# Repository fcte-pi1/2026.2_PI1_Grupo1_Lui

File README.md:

# Projeto Integrador 1 - 2026.2 | Grupo 01 | Prof. Lui

<div align="center">

  # Projeto Integrador 1 — Micromouse (Grupo 1)
  **Semestre 2026.2 | Universidade de Brasília (UnB) | Prof. Lui**

</div>

---

> **Aviso ao Professor:** Este é o repositório oficial do Grupo 01 utilizado para o desenvolvimento do projeto de PI1 (Micromouse) durante o semestre 2026.2. Todo o histórico de commits, código-fonte e detalhamentos estão centralizados aqui.

## 🤖 Sobre o Projeto
O projeto consiste no desenvolvimento completo de um robô autônomo (Micromouse) capaz de navegar e resolver um labirinto, integrando conhecimentos de quatro grandes áreas da engenharia: **Software, Eletrônica, Energia e Estruturas**.

Toda a documentação gerencial e conceitual (TAP, Requisitos, EAP, Cronograma, Testes, etc.) está centralizada de forma interativa no nosso **[Site de Documentação Oficial](https://fcte-pi1.github.io/2026.2_PI1_Grupo1_Lui/)**.

## 🗂️ Estrutura do Repositório
Para manter o padrão e a facilidade de busca, o repositório está dividido nas seguintes pastas:

* 📂 **`docs/`** — Arquivos Markdown (`.md`) e ativos que alimentam a página web.
* 📂 **`hw/`** — Arquitetura de hardware, esquemáticos e arquivos de simulação de circuitos.
* 📂 **`mec/`** — Modelagens 3D, arquivos CAD e projetos de estrutura.
* 📂 **`src/`** — Código-fonte e algoritmos de navegação/controle do robô.

*(A estrutura de pastas não isola as equipes. O projeto é multidisciplinar e os membros devem trabalhar nas diferentes pastas conforme a necessidade das tarefas).*

## 👥 Equipe
O time é formado por estudantes de engenharia e dividido em subáreas para facilitar o gerenciamento técnico, atuando sob a liderança geral de **Antônio Lucas** e apoio dos subgerentes:

* 💻 **Software:** Pedro Ian (Subgerente)
* ⚡ **Energia:** Rafaela Trajano (Subgerente)
* 🔌 **Eletrônica:** Leonardo Augusto (Subgerente)
* 🏗️ **Estruturas:** Carlos Henrique (Subgerente)

<details>
<summary><b>Clique aqui para ver a lista completa com os 19 integrantes</b></summary>

* Humberto Alencar (Aeroespacial)
* João Vitor Sales Ibiapina (Software)
* Eduardo Lobo Moreira (Software)
* Pedro Ian (Software)
* Breno Teixeira (Software)
* Rafaela Trajano Ruas (Energia)
* Lucas Oliveira de Paula (Software)
* Carlos Henrique de Paiva Muniz (Software)
* Mariana Solano de Brito Elias (Aeroespacial)
* Antônio José Magalhães Leão Júnior (Software)
* João Pedro Jaime (Software)
* Lucas Peixoto Rodrigues (Software)
* Daniel Almeida Frota (Software)
* Antônio Lucas De Araújo Lima (Software)
* Pedro Franco Cavalcanti Rêgo (Software)
* Alexandre Henrique Almeida Valadares Sousa (Software)
* Davi Sakai (Software)
* Gustavo Antônio (Software)
* Leonardo Augusto (Eletrônica)

</details>

## 🚀 Para os Integrantes: Como Contribuir

A organização e a correta utilização do repositório serão consideradas na avaliação do grupo. Dessa forma, é fundamental que **todos** utilizem o Git de forma alinhada com a estratégia da equipe.

### Fluxo de Trabalho
1. **Clone o repositório:** Após obter acesso (via convite no e-mail ou notificação), abra o terminal e clone o projeto:
   ```bash
   git clone [https://github.com/fcte-pi1/2026.2_PI1_Grupo1_Lui.git](https://github.com/fcte-pi1/2026.2_PI1_Grupo1_Lui.git)

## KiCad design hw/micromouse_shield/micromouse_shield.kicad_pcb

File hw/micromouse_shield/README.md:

# Projeto KiCad — PCB Shield do Micromouse (Grupo 1)

Este diretório contém os arquivos de projeto da placa de circuito impresso (**PCB Shield customizada**) do robô autônomo Micromouse para a disciplina **PI1 (2026.2, FCTE/UnB, Prof. Lui)**.

O projeto é 100% compatível com as versões **KiCad v7, v8, v9 e v10** com biblioteca embutida (*Self-Contained*), permitindo que qualquer integrante da equipe (inclusive de Software) abra e visualize o esquemático em qualquer computador sem precisar instalar bibliotecas externas. Além disso, um arquivo PDF já renderizado está disponível no próprio diretório para visualização imediata.

---

## 1. Estrutura dos Arquivos

```
hw/micromouse_shield/
├── micromouse_shield.kicad_pro        # Arquivo de configuração e metadados do projeto KiCad
├── micromouse_shield.kicad_sch        # Esquemático elétrico oficial sincronizado (Rev 2.0)
├── micromouse_shield_VERSION2.kicad_sch # Arquivo de esquemático Rev 2.0 (com proteções e Buck)
├── micromouse_shield.kicad_pcb        # PCB populada com todos os footprints oficiais, posições e furos M3
├── micromouse_shield.pdf              # PDF em alta resolução do esquemático para consulta rápida
├── micromouse_shield_sch.png          # Imagem PNG em alta resolução (300 DPI) do esquemático Rev 2.0
├── micromouse_shield_3d.png           # Renderização 3D oficial da placa Shield montada
├── micromouse_shield.net              # Netlist elétrica para verificação e importação
├── diagrama_blocos_hardware.png       # Imagem em alta resolução do Diagrama de Blocos do robô
├── diagrama_blocos_hardware.tex       # Código-fonte TikZ (LaTeX Standalone) do Diagrama de Blocos
├── diagrama_blocos_hardware.mmd       # Código-fonte Mermaid do Diagrama de Blocos
├── generate_schematic.py              # Script Python reprodutível gerador do esquemático
├── generate_pcb.py                    # Script Python reprodutível gerador da PCB via pcbnew nativo
└── README.md                          # Guia de montagem e instruções de layout
```

---

## 2. Como Abrir e Visualizar no KiCad

1. No terminal do CachyOS/Linux (ou no menu de aplicativos), execute:
   ```bash
   kicad hw/micromouse_shield/micromouse_shield.kicad_pro
   ```
2. Na janela principal do KiCad:
   - Dê duplo clique em **`micromouse_shield.kicad_sch`** (ou abra `micromouse_shield_VERSION2.kicad_sch`) para abrir o editor esquemático (**Eeschema**);
   - Ou dê duplo clique em **`micromouse_shield.kicad_pcb`** para abrir o editor de PCB (**Pcbnew**);
3. Dica rápida: Se quiser apenas consultar as conexões sem abrir o KiCad, abra diretamente o arquivo [`micromouse_shield.pdf`](file:///home/eduardolm/Documents/2026.2_PI1_Grupo1_Lui/hw/micromouse_shield/micromouse_shield.pdf) ou visualize [`micromouse_shield_sch.png`](file:///home/eduardolm/Documents/2026.2_PI1_Grupo1_Lui/hw/micromouse_shield/micromouse_shield_sch.png).

---

## 3. Arquitetura do Esquemático e Mapeamento de Redes (*Nets*) (Rev 2.0)

O circuito adota a topologia **100% Plug & Play**, utilizando apenas barras de pinos fêmea (soquetes de 2,54 mm) para receber módulos prontos e conectores com trava:

| Bloco Funcional | Referência | Componente / Módulo | Conexões e Rótulos de Redes (*Nets*) |
|---|:---:|---|---|
| **Processamento Central** | `J_ESP_L` e `J_ESP_R` | Barras Fêmea 1x15 para ESP32 DevKit V1 | Todos os 30 pinos mapeados, com GPIO 12 isolado contra travamento de boot. |
| **Driver de Motores** | `J_DRV_CTRL` e `J_DRV_PWR` | Barras Fêmea 1x08 para módulo TB6612FNG | PWM (`PWMA`, `PWMB`), Direção (`AIN1/2`, `BIN1/2`), saídas dos motores e alimentação $V_{MOT}$. |
| **IMU Inercial** | `U_IMU` | Barra Fêmea 1x08 para GY-521 (MPU6050) | $I^2C$ (`I2C_SDA` no GPIO 21, `I2C_SCL` no GPIO 22) e alimentação de 3,3 V. |
| **Sensores de Distância** | `J_TOF_F`, `J_TOF_L`, `J_TOF_R` | Barras Macho 1x05 para 3x VL53L0X | $I^2C$ compartilhado + pinos de corte dinâmico `XSHUT_F` (GPIO 32), `XSHUT_L` (GPIO 13), `XSHUT_R` (GPIO 14). |
| **Atuadores e Encoders** | `J_MOT_L` e `J_MOT_R` | Conectores JST 1x06 para motores N20 | Alimentação de motor e sinais de quadratura alimentados estritamente em **3,3 V** (`ENC_L_A/B` e `ENC_R_A/B`). |
| **Entrada de Bateria** | `TB_PWR1` | Borne/Conector Polarizado 2 vias | 1: $V_{BAT}+$ (7,4 V), 2: $GND$. |
| **Proteção por Fusível** | `F1` | Fusível Rearmável 3A | Em série com o polo positivo da bateria. |
| **Chave Geral Mecânica** | `SW1` | Chave Mecânica Liga/Desliga | Interrupção física do barramento de alimentação. |
| **Proteção Polaridade**  | `Q1` e `R_G1` | MOSFET Canal P (AO3401A) + 10 k$\Omega$ | Proteção ativa contra inversão de polaridade com perda desprezível. |
| **Conversor Buck (5V)**  | `J_BUCK1` | Barra Fêmea 1x04 para Módulo Step-Down | 1: VIN+, 2: VIN-, 3: VOUT+ (5V), 4: VOUT- (GND). |
| **Proteção Anti-Brownout**| `C_BULK1` e `C_OUT1` | Capacitores Eletrolíticos 470 µF e 100 µF | $C_{BULK1}$ colado aos pinos de potência do TB6612FNG; $C_{OUT1}$ na linha 5V. |
| **Divisor de Bateria**    | `R_DIV3`, `R_DIV4`, `C_DIV1` | Divisor Resistivo com Capacitor de Filtro | Saída atenuada ligada ao pino analógico `ADC_BAT_SENSE` (GPIO 34). |
| **IHM / Sinalização**     | `J_BUZ`, `J_RGB`, `SW_START` | Módulos KY-012, WS2812B e Botão THT | `BUZZER_SIG` (GPIO 4), `LED_RGB_DIN` (GPIO 2), `START_BTN` (GPIO 15 direto ao GND via `INPUT_PULLUP`). |

---

## 4. Passos para Gerar o Layout da Placa (PCB)

Para transformar o esquemático na placa física de circuito impresso:

1. No editor esquemático (**Eeschema**), aperte a tecla **`F8`** (ou clique em *Tools $\rightarrow$ Update PCB from Schematic*);
2. Clique em **Update PCB** para carregar todas as pegadas (*footprints*) no editor de PCB (**Pcbnew**);
3. **Disposição Recomendada dos Componentes no Chassi:**
   - **Bico Dianteiro:** Conector `J_TOF_F` (0°) centralizado; conectores `J_TOF_L` e `J_TOF_R` nas laterais apontando para 90°;
   - **Centro:** Soquetes `J_ESP_L` e `J_ESP_R` (com a ponta da antena voltada para a borda externa desobstruída);
   - **Laterais Traseiras:** Conectores `J_MOT_L` e `J_MOT_R` próximos aos motores N20;
   - **Traseira:** Borne de alimentação `TB_PWR` com fácil acesso para o chicote da bateria;
   - **Topo:** Módulo LED RGB, Buzzer e Botão de Largada.
4. **Regras de Roteamento:**
   - Trilhas de potência ($V_{MOT}$, saídas de motor e $GND$): largura mínima de **$1{,}2\,\text{mm}$**;
   - Trilhas de sinais lógicos e $I^2C$: largura de **$0{,}3\,\text{mm}$**;
   - Preenchimento de cobre inferior e superior com plano de terra unificado (**GND**).

---

## 5. Como Exportar Arquivos Gerber para Fabricação

Quando o layout das trilhas estiver concluído:
1. No **Pcbnew**, clique em **File $\rightarrow$ Fabrication Outputs $\rightarrow$ Gerbers (.gbr)**;
2. Selecione as camadas: `F.Cu`, `B.Cu`, `F.Mask`, `B.Mask`, `F.Silkscreen`, `B.Silkscreen`, `Edge.Cuts`;
3. Clique em **Generate Drill File** para gerar os furos (.drl);
4. Compacte todos os arquivos gerados em um arquivo `.zip` e envie para o fabricante (ex.: JLCPCB, PCBWay ou usinagem da UnB).

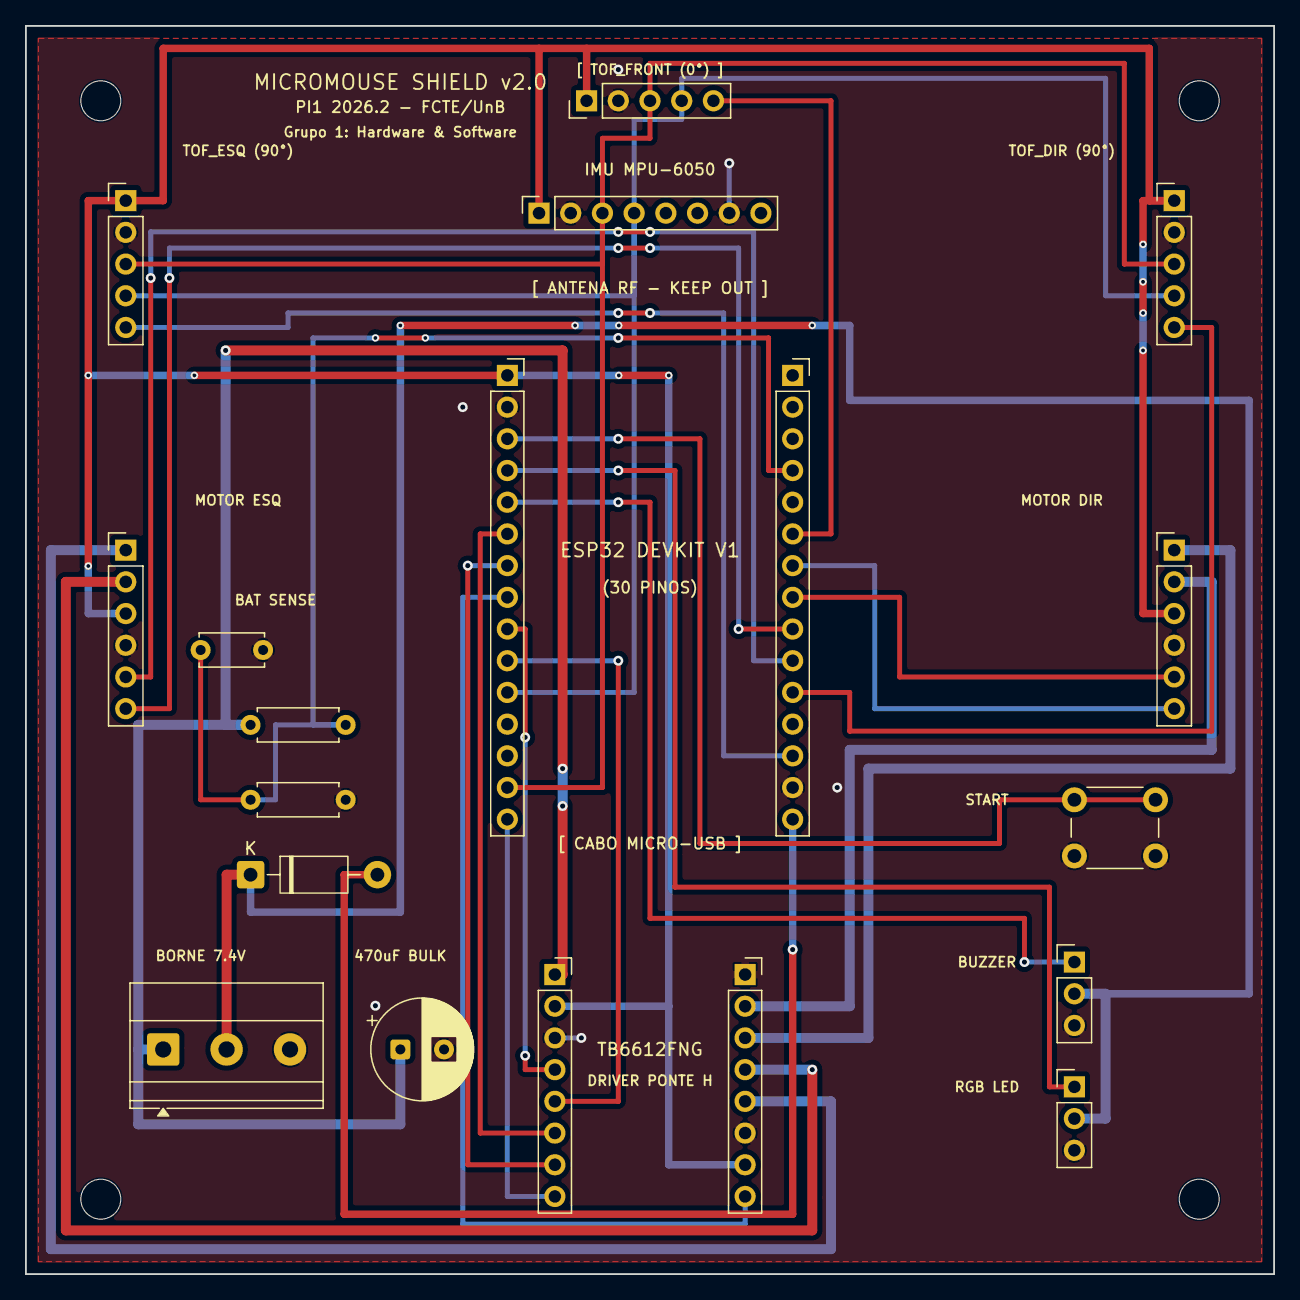
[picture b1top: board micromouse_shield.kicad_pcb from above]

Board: 2 copper layers, 100.0 x 100.0 mm, 23 parts (0 on the bottom side), 28 nets.

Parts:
C_BULK: 470uF_16V; CP_Radial_D8.0mm_P3.50mm
C_DIV: 100nF; C_Disc_D5.0mm_W2.5mm_P5.00mm
D_USB_PROT: 1N5819; D_DO-41_SOD81_P10.16mm_Horizontal
H1, H2, H3, H4: M3; MountingHole_3.2mm_M3
J_BUZ: BUZZER; PinHeader_1x03_P2.54mm_Vertical
J_DRV_CTRL: TB6612_CTRL; PinSocket_1x08_P2.54mm_Vertical
J_DRV_PWR: TB6612_PWR; PinSocket_1x08_P2.54mm_Vertical
J_ESP_L: ESP32_LEFT; PinSocket_1x15_P2.54mm_Vertical
J_ESP_R: ESP32_RIGHT; PinSocket_1x15_P2.54mm_Vertical
J_MOT_L: MOTOR_ESQ; PinHeader_1x06_P2.54mm_Vertical
J_MOT_R: MOTOR_DIR; PinHeader_1x06_P2.54mm_Vertical
J_RGB: RGB_LED; PinHeader_1x03_P2.54mm_Vertical
J_TOF_F: TOF_FRONT; PinHeader_1x05_P2.54mm_Vertical
J_TOF_L: TOF_LEFT; PinHeader_1x05_P2.54mm_Vertical
J_TOF_R: TOF_RIGHT; PinHeader_1x05_P2.54mm_Vertical
R_DIV1: 100k; R_Axial_DIN0207_L6.3mm_D2.5mm_P7.62mm_Horizontal
R_DIV2: 33k; R_Axial_DIN0207_L6.3mm_D2.5mm_P7.62mm_Horizontal
SW_START: BOTAO_START; SW_PUSH_6mm
TB_PWR: BORNE_ALIM_7V4; TerminalBlock_Phoenix_MKDS-1,5-3-5.08_1x03_P5.08mm_Horizont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
U_IMU: MPU6050; PinSocket_1x08_P2.54mm_Vertical

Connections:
ADC_BAT_SENSE: C_DIV.1, J_ESP_R.4, R_DIV1.2, R_DIV2.1
AIN1: J_DRV_CTRL.4, J_ESP_L.9
AIN2: J_DRV_CTRL.5, J_ESP_L.10
BIN1: J_DRV_CTRL.8, J_ESP_L.15
BIN2: J_DRV_PWR.8, J_ESP_L.8
BUZZER_SIG: J_BUZ.1, J_ESP_L.5
ENC_L_A: J_ESP_R.10, J_MOT_L.5
ENC_L_B: J_ESP_R.9, J_MOT_L.6
ENC_R_A: J_ESP_R.8, J_MOT_R.5
ENC_R_B: J_ESP_R.7, J_MOT_R.6
GND: C_BULK.2, C_DIV.2, J_BUZ.3, J_DRV_CTRL.3, J_DRV_PWR.1, J_DRV_PWR.6, J_ESP_L.2, J_ESP_R.14, J_MOT_L.4, J_MOT_R.4, J_RGB.3, J_TOF_F.2, J_TOF_L.2, J_TOF_R.2, R_DIV2.2, SW_START.2, TB_PWR.3, U_IMU.2, U_IMU.7
I2C_SCL: J_ESP_L.14, J_TOF_F.3, J_TOF_L.3, J_TOF_R.3, U_IMU.3
I2C_SDA: J_ESP_L.11, J_TOF_F.4, J_TOF_L.4, J_TOF_R.4, U_IMU.4
LED_RGB_DIN: J_ESP_L.4, J_RGB.1
MOT_L_N: J_DRV_PWR.4, J_MOT_L.2
MOT_L_P: J_DRV_PWR.5, J_MOT_L.1
MOT_R_N: J_DRV_PWR.2, J_MOT_R.2
MOT_R_P: J_DRV_PWR.3, J_MOT_R.1
PWMA: J_DRV_CTRL.6, J_ESP_L.6
PWMB: J_DRV_CTRL.7, J_ESP_L.7
START_BTN: J_ESP_L.3, SW_START.1
VCC_3V3: J_DRV_CTRL.2, J_DRV_PWR.7, J_ESP_L.1, J_MOT_L.3, J_MOT_R.3, J_TOF_F.1, J_TOF_L.1, J_TOF_R.1, U_IMU.1
VCC_5V: D_USB_PROT.1, J_BUZ.2, J_RGB.2, TB_PWR.2
VCC_5V_ESP: D_USB_PROT.2, J_ESP_R.15
VMOT: C_BULK.1, J_DRV_CTRL.1, R_DIV1.1, TB_PWR.1
XSHUT_F: J_ESP_R.6, J_TOF_F.5
XSHUT_L: J_ESP_R.13, J_TOF_L.5
XSHUT_R: J_ESP_R.11, J_TOF_R.5

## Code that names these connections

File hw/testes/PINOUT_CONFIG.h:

#pragma once

/**
 * ==============================================================================
 * MAPEAMENTO GERAL DE PORTAS E PINOS - MICROMOUSE PI1 2026.2 (SHIELD REV 2.0)
 * ==============================================================================
 */

// I2C (Sensores ToF VL53L0X, Display OLED SSD1306, IMU MPU6050)
#define PIN_I2C_SDA         21
#define PIN_I2C_SCL         22

// Controle XSHUT dos Sensores ToF
#define PIN_XSHUT_FRONT     32  // Sensor Frontal (0 grau) - Principal
#define PIN_XSHUT_LEFT      13  // Sensor Esquerdo (90 graus)
#define PIN_XSHUT_RIGHT     14  // Sensor Direito (90 graus)

// Ponte H TB6612FNG (Motores DC N20)
#define PIN_PWMA            16  // Modulacao PWM Motor Esquerdo (20 kHz)
#define PIN_PWMB            17  // Modulacao PWM Motor Direito (20 kHz)
#define PIN_AIN1            18  // Sentido A Motor Esquerdo
#define PIN_AIN2            19  // Sentido B Motor Esquerdo
#define PIN_BIN1            23  // Sentido A Motor Direito
#define PIN_BIN2             5  // Sentido B Motor Direito

// Encoders em Quadratura (Leitura de pulsos dos motores)
#define PIN_ENC_L_A         27  // Canal A Encoder Esquerdo (Interrupcao)
#define PIN_ENC_L_B         26  // Canal B Encoder Esquerdo
#define PIN_ENC_R_A         25  // Canal A Encoder Direito (Interrupcao)
#define PIN_ENC_R_B         33  // Canal B Encoder Direito

// Interface Homem-Maquina (IHM)
#define PIN_BUTTON_START    15  // Botao fisico de largada (Pull-up interno)
#define PIN_RGB_LED          2  // LED de sinalizacao visual
#define PIN_BUZZER           4  // Buzzer piezoeletrico ativo (>= 60 dB)

// Monitoramento Eletrico / Bateria
#define PIN_ADC_BATTERY     34  // Leitura analogica do divisor de tensao (ADC1_CH6)

// Isolamento
#define PIN_BOOT_ISOLATED   12  // Isolado na Shield para evitar falha de boot
